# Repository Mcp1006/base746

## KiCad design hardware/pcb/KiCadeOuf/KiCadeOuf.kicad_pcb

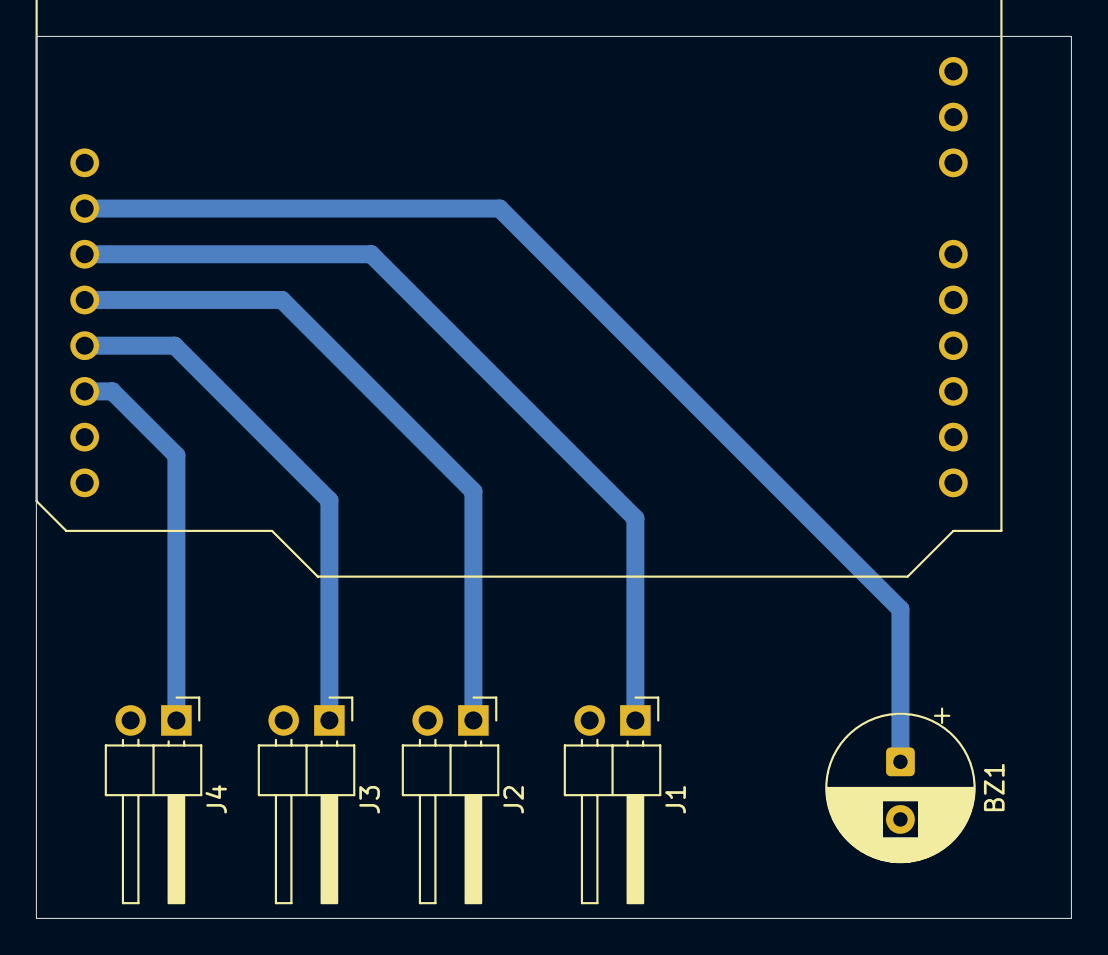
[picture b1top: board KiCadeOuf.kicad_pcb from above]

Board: 2 copper layers, 57.5 x 49.0 mm, 6 parts (0 on the bottom side), 6 nets.

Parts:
A1: Arduino_UNO_R3
BZ1: Buzzer; CP_Radial_D8.0mm_P3.50mm
J1: BP4; PinHeader_1x02_P2.54mm_Horizontal
J2: BP3; PinHeader_1x02_P2.54mm_Horizontal
J3: BP2; PinHeader_1x02_P2.54mm_Horizontal
J4: BP1; PinHeader_1x02_P2.54mm_Horizontal

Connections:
GND: A1.6 (GND), A1.7 (GND), BZ1.2 (-), J1.2, J2.2, J3.2, J4.2
unnamed: A1.17 (D2), J4.1
unnamed: A1.18 (D3), J3.1
unnamed: A1.19 (D4), J2.1
unnamed: A1.20 (D5), J1.1
unnamed: A1.21 (D6), BZ1.1 (+)

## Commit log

2026-06-15 Commit initial
2026-06-15 Ajout des fichiers de conception KiCad et FreeCAD
2026-06-15 Ajout des sons
2026-06-18 Ajout du STEP
